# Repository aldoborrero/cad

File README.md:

# cad

My CAD projects in one repo, with the toolchain pinned so a checkout builds the same
parts on any machine.

Every part is **source, not a binary**: an OpenSCAD script, a FreeCAD Python model, or a
KiCad project. Parts diff and merge like code, the numbers behind them are readable, and
everything under `exports/` is rebuilt on demand rather than committed.

## What's here

**Three kernels, because none of them is good at everything.** A part lives with the tool
that suits it, and a part that wants two of them gets two:

| | Good at | Entry file |
|---|---|---|
| **OpenSCAD** | fast parametric iteration, mesh/CSG | `<project>/openscad/<project>.scad` |
| **FreeCAD** (Python) | OCCT **B-rep** — real fillets and chamfers, native STEP | `<project>/freecad/<project>.py` |
| **KiCad** | the electrical side; hands the board to the other two as STEP | `<project>/kicad/<project>.kicad_pro` |

**One reproducible shell.** `nix develop` gives you all three plus the OpenSCAD libraries
(BOSL2, Round-Anything), a linter, and the export tooling — no system installs, same
versions everywhere.

**One command for the boring parts.** `cad export`, `cad render`, `cad gui`, `cad new`
work the same whichever kernel a project uses.

**ECAD meets MCAD.** FreeCAD carries the [KiCadStepUp][ksu] workbench, wired to KiCad's
3D model library, so a board opens in FreeCAD with its components on it and mechanical
constraints can travel back to the board outline.

**Two MCP servers**, so an LLM can drive either kernel: `freecad-mcp` for FreeCAD, and
[Konnect][kon] for KiCad — 187 tools over KiCad 10's official IPC API, loaded on demand.
Both are on PATH in the devshell; register them with your MCP client. Don't run `konnect`
bare in a terminal — it reads a TTY as "install yourself into `~/.claude`".

[ksu]: https://github.com/easyw/kicadStepUpMod
[kon]: https://github.com/mixelpixx/Konnect

## Projects

| Project | Kernels | What it is |
|---|---|---|
| [**marble-run**](projects/marble-run/openscad/) | OpenSCAD (+ FreeCAD for one piece) | A 3D-printable **Hape Quadrilla**-compatible marble run: **34 parts** across blocks, rails, ramps, connectors, mechanisms, towers and catchers, all derived from one measured set of dimensions (`SIDE=44`, `HEIGHT=60`, Ø16 marble). Channel geometry is a faithful port of [`shuckc/quadri-plot`][qp]. Ships a `pybullet` bench that drops marbles through the mechanisms, and a checker that builds every part and asserts on its mesh. |
| [**iotorero-mount**](projects/iotorero-mount/) | OpenSCAD + FreeCAD | Outlet cradle for the round Athom / IoTorero IR remote (RF + IR, USB-C, ~20 g). It rests on the USB charger in a Schuko socket, with the puck hanging below and spare cable in a snap-in clip. Built **twice**, once per kernel, as a side-by-side mesh-vs-B-rep reference. |

[qp]: https://github.com/shuckc/quadri-plot

> The charger-brick dimensions in `iotorero-mount` (`BRICK_W` / `BRICK_H`) are
> placeholders — measure yours before printing.

## Getting started

```sh
direnv allow          # .envrc: `use flake` + `PATH_add bin`
# ...or, without direnv:
nix develop           # then run ./bin/cad
```

```sh
cad ls                            # what's in here
cad export marble-run             # STL + 3MF into projects/marble-run/openscad/exports/
cad render iotorero-mount/openscad side
cad gui marble-run
```

## The `cad` helper

An optional [KiCad Backplane package](docs/kicad-backplane.md) supplies a
headless IPC server: `nix run .#kicad-backplane -- api-server --help`.
It is built separately and does not replace KiCad on the devshell PATH.

| Command | Does |
|---|---|
| `cad ls` | list every project, as `project/tool` |
| `cad new openscad\|freecad\|kicad NAME` | scaffold from `templates/<tool>/` |
| `cad render NAME [VIEW]` | PNG preview → `exports/` (OpenSCAD and KiCad) |
| `cad export NAME` | OpenSCAD → STL + 3MF · FreeCAD → STEP + STL · KiCad → STEP |
| `cad step NAME` | OpenSCAD → STEP via FreeCAD (best-effort) |
| `cad gui NAME` | open in OpenSCAD / FreeCAD / KiCad |

`NAME` is a path under `projects/` with the tool part optional: `marble-run`,
`marble-run/ramps/accelerator`, `iotorero-mount/openscad`. A bare name resolves by itself
when only one kernel has the part, and asks you to say which when both do.

`VIEW` is a camera for OpenSCAD (`iso|fit|top|front|side`) and a side of the board for
KiCad (`iso|top|bottom|front|back|left|right`).

## Layout

```
projects/<project>/{openscad,freecad,kicad}/    the parts; exports/ is generated
templates/{openscad,freecad,kicad}/             what `cad new` copies
lib/openscad/                                   shared helpers: `use <common.scad>`
bin/cad                                         the helper
nix/                                            devshell, packages, checks
```

A tool directory holds only that kernel's source. A project with tooling of its own keeps
it one level up, beside them — `marble-run` has `sim/` and `tools/` (Python that drives
OpenSCAD) plus a `bin/` and an `.envrc`, so `cd projects/marble-run` and `play` or `check`
are on PATH.

Project-first on purpose: a part that exists in two kernels is *one* directory with both
inside, not the same name in two corners of the repo.

Source of truth is the `.scad` / `.py` / the KiCad project files. Everything under
`exports/` is generated and git-ignored — don't commit it.

## Licensing

The parts in `projects/` are mine. Everything the devshell pulls in is somebody else's
and keeps its own licence — this repo packages it, it does not relicense it.

The table below is **generated from the flake**, so it cannot drift from what is actually
installed: `nix run .#update-licenses` regenerates it, and `nix flake check` fails both
when it is stale and when an input has been added that `nix/lib/default.nix` does not
classify. Copyleft licences are bolded, since those are the ones worth noticing.

<!-- BEGIN LICENCES -->
<!-- Generated by `nix run .#update-licenses`. Do not edit by hand. -->

### On PATH in the devshell

| | Licence | What it is |
|---|---|---|
| [ShellCheck](https://hackage.haskell.org/package/ShellCheck) 0.11.0 | **GPL-3.0-only** | Shell script analysis tool |
| [freecad](https://www.freecad.org) 1.1.1 | LGPL-2.0-or-later | General purpose Open Source 3D CAD/MCAD/CAx/CAE/PLM modeler, with the MCP and Gridfinity workbenches and this repo's preferences |
| [freecad-mcp](https://github.com/neka-nat/freecad-mcp) 0.1.21 | MIT | MCP server for FreeCAD: drives a running FreeCAD over XML-RPC |
| [freerouting](https://www.freerouting.org) 2.2.4 | **GPL-3.0-only** | Advanced PCB auto-router |
| [kicad](https://www.kicad.org/) 10.0.4 | **GPL-3.0-or-later** | Open Source Electronics Design Automation suite |
| [konnect](https://github.com/mixelpixx/Konnect) 0.11.0 | **AGPL-3.0-only** | MCP server for KiCad 10: drives a running KiCad over its IPC API |
| [openscad-lsp](https://github.com/Leathong/openscad-LSP) 2.0.2 | Apache-2.0 | LSP (Language Server Protocol) server for OpenSCAD |
| [openscad-unstable](https://openscad.org/) 2021.01-unstable-2026-07-20 | **GPL-3.0** | 3D parametric model compiler (unstable) |
| [orca-slicer](https://github.com/OrcaSlicer/OrcaSlicer) 2.4.2 | **AGPL-3.0-only** | G-code generator for 3D printers (Bambu, Prusa, Voron, VzBot, RatRig, Creality, etc.) |
| [python3](https://www.python.org) | Python-2.0 | High-level dynamically-typed programming language |
| [sca2d](https://gitlab.com/bath_open_instrumentation_group/sca2d) 0.2.2 | **GPL-3.0-only** | Experimental static code analyser for OpenSCAD |
| [xvfb-run](https://github.com/archlinux/svntogit-packages) 1+g87f6705 | **GPL-2.0-only** | Convenience script to run a virtualized X-Server |

### Optional packages (not on the devshell PATH)

| | Licence | What it is |
|---|---|---|
| [kicad-backplane](https://github.com/i2cjak/Backplane_KiCad) 10.0.6-backplane-1c193606edde | **GPL-3.0-or-later** | KiCad 10.0.6 with Backplane headless PCB and schematic IPC backports |

### Vendored as source (FreeCAD addons, OpenSCAD libraries)

| | Licence | What it is |
|---|---|---|
| [bosl2](https://github.com/BelfrySCAD/BOSL2) | BSD-2-Clause | OpenSCAD library: rounded solids, attachments, threads, gears |
| [curves](https://github.com/tomate44/CurvesWB) | LGPL-2.0 | FreeCAD workbench: NURBS curve and surface tools |
| [gridfinity](https://github.com/Stu142/FreeCAD-Gridfinity-Workbench) | LGPL-2.0 | FreeCAD workbench: Gridfinity storage bins |
| [kicad-stepup](https://github.com/easyw/kicadStepUpMod) | **AGPL-3.0** | FreeCAD workbench: bidirectional KiCad <-> FreeCAD (ECAD/MCAD) |
| [round-anything](https://github.com/Irev-Dev/Round-Anything) | MIT | OpenSCAD library: 2D/3D rounding (polyRound) |
<!-- END LICENCES -->

Two worth knowing about. **Konnect is AGPL-3.0** — free for individuals and open source,
commercial licences sold separately — so it is the one to check before using it at work.
And **KiCadStepUp declares AGPLv3 in its `package.xml` but ships no `LICENSE` file**, so
the full text is not in the tree.

This repo itself carries no `LICENSE`, which under copyright law means all rights
reserved. That is the default, not a decision; add one if you ever publish it.

## Notes to self

[`CLAUDE.md`](CLAUDE.md) is the long-form version of all of the above: the conventions,
and a **Gotchas** section recording the traps that cost real time here (OpenSCAD's
Manifold backend, BOSL2's globals shadowing, FreeCAD's addon and preference mechanics,
KiCad's compressed 3D models). [`CHANGELOG.md`](CHANGELOG.md) has what changed and why.

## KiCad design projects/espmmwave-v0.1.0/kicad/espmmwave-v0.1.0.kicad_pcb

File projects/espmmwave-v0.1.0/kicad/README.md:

# espmmwave-v0.1.0 (KiCad)

The board and schematic for the ESPHome LD2450 presence sensor. **The project manual —
bill of materials, datasheets, differences from the original and credits — is one level up
in [`../README.md`](../README.md).** This file covers only what is specific to the KiCad
half.

The usual trio, all sharing the project's name: `espmmwave-v0.1.0.kicad_pro`,
`.kicad_sch` and `.kicad_pcb`, plus this project's own libraries — `espmmwave.kicad_sym`
and `espmmwave.pretty/` — which hold the XIAO ESP32S3 symbol and footprint that KiCad does
not ship.

## Both files are source; the geometry can still be rebuilt

**`.kicad_pcb` is edited.** It can be *rebuilt* from the measured geometry in
`../tools/board.py`, which parses it out of the original's gerbers — something KiCad has no
way to do — but that is a bootstrap, not the daily path.

```sh
board --regenerate   # -> .kicad_pcb, from the measured geometry and the schematic's netlist
```

**Both files are edited and kept**, in eeschema and pcbnew or through the Konnect MCP
server. They began life generated, which is why they agree, but that is now a property to be
*checked* rather than one the tooling can guarantee:

```sh
check        # the everyday command: do the board and the sheet still agree?
```

`board` refuses to write without `--regenerate`: it rebuilds the whole file and every run
mints fresh UUIDs, so there is nothing to merge — what it writes replaces everything. There
is no schematic generator any more; eeschema and Konnect both write schematics perfectly
well, and one description of the circuit is enough.

## Checking it

`check` runs three checks, and they fail for different reasons:

| Check | Catches |
|---|---|
| connectivity | the board's pad-to-net assignment, against the netlist KiCad exports from the sheet |
| annotation | every symbol's instance reference and root-sheet path |
| ERC | KiCad's own electrical rules |

The middle one is not redundant. **`kicad-cli sch erc` resolves a symbol's reference from its
`Reference` property, while eeschema resolves it from the `instances` block** — so a file can
report 0 violations and still open full of duplicate, unannotated `#PWR?` symbols. That is a
defect this project actually shipped; the repo's `CLAUDE.md` records the trap. Run ERC in the
GUI too.

The board keeps its own:

```sh
kicad-cli pcb drc --severity-all -o /tmp/drc.rpt espmmwave-v0.1.0.kicad_pcb
```

## Handoff to the mechanical side

```sh
cad export espmmwave-v0.1.0     # -> exports/espmmwave-v0.1.0.step
cad render espmmwave-v0.1.0 iso # -> exports/espmmwave-v0.1.0-iso.png
```

The STEP is what FreeCAD opens to check the board against the Hammond 1551V3GY case and the
LD2450 bracket. Importing the `.kicad_pcb` directly with the **KiCadStepUp** workbench works
too, and resolves each footprint's 3D model against the library the devshell's `kicad`
ships.

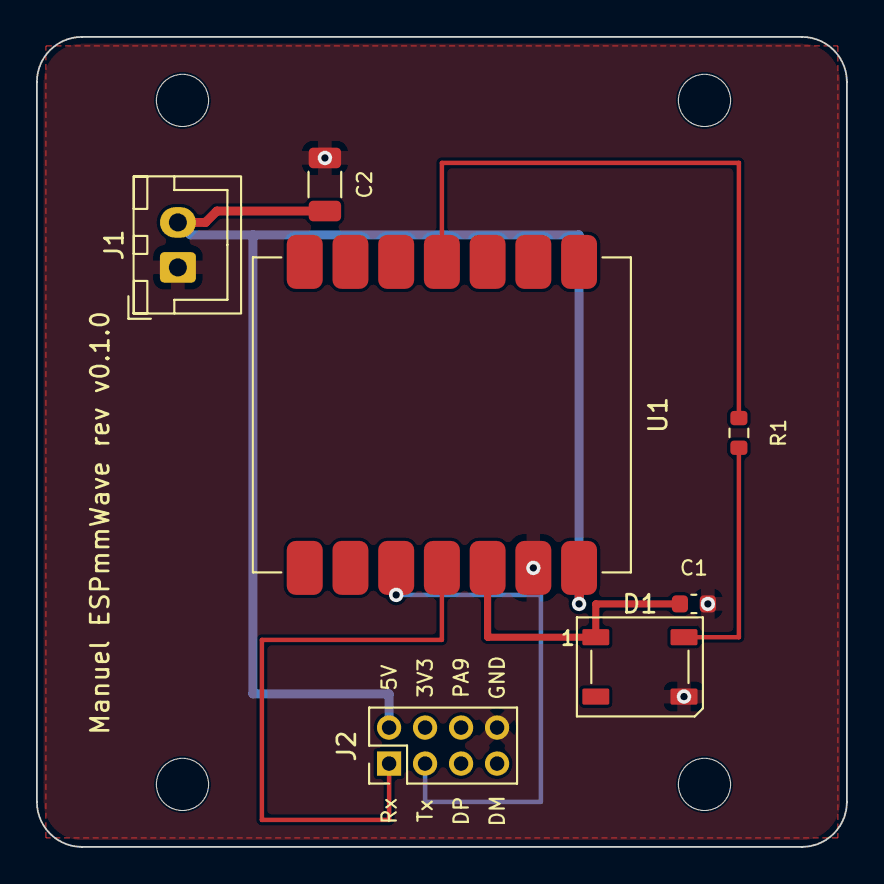
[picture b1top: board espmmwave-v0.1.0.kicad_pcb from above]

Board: 2 copper layers, 45.0 x 45.0 mm, 7 parts (0 on the bottom side), 7 nets.

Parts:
C1: C_0603_1608Metric
C2: C_1206_3216Metric
D1: LED_WS2812B_PLCC4_5.0x5.0mm_P3.2mm
J1: JST_XH_B2B-XH-A_1x02_P2.50mm_Vertical
J2: PinHeader_2x04_P2.00mm_Vertical
R1: R_0603_1608Metric
U1: XIAO_ESP32S3

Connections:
+3V3: C1.1, D1.1, U1.3V3
+5V: C2.1, J1.2, J2.2, U1.5V
GND: C1.2, C2.2, D1.3, J1.1, J2.8, U1.GND
LED_DATA: R1.2, U1.D3
LED_DIN: D1.4, R1.1
RADAR_RX: J2.1, U1.D10
RADAR_TX: J2.3, U1.D9

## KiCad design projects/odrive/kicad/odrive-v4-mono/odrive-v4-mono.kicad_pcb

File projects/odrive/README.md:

# odrive (KiCad)

ODrive brushless motor controller: a faithful KiCad 10 recreation of the v3.5
schematic, and a v4 redesign derived from it.

Upstream: [madcowswe/ODriveHardware](https://github.com/madcowswe/ODriveHardware)
(Altium sources; we work from a local fork clone). Firmware is open source (MIT) at
odriverobotics/ODrive up to v0.5.6, which supports every v3.x board.

## Layout

```
docs/
  v3.5-weaknesses.md    # audited weak points of the v3.5 design (workflow phase: Audit)
  v4-design.md          # v4 design decisions with rationale (workflow phase: Design)
kicad/
  odrive-v3.5/          # faithful v3.5 schematic (no PCB) — the audited baseline
  odrive-v4/            # the v4: schematic + 4-layer board
workflow/
  e2e.js                # oracle-gated end-to-end Workflow script (see below)
```

Reference material lives in `.scratch/odrive/` at the repo root (gitignored, per repo
convention): `schematic_v3.5.pdf` (the 24V variant), `CHANGELOG.md`, board photos, and
`netlist-ref/` (netlist ground truth extracted from the PDF by the workflow). Refresh
from `/mnt/c/Users/aldob/dev/ODriveHardware/v3/` if missing.

## Scope decisions (2026-09-03)

- **Architecture: modernized.** Keep STM32F405RGT6 (firmware nearly intact); replace
  the NRND DRV8301 with DRV8353RS (100 V, SPI, integrated buck + 3 CSAs); modern FETs;
  USB-C; better CAN; add the protections v3.5 lacks.
- **Bus voltage: both variants.** One design, two BOMs — 24 V and 56 V.
- **v3.5 conversion: faithful schematic only.** Clean ERC, netlist checked against the
  PDF (which embeds the Altium netlist as text). No v3 PCB recreation.
- **Form factor: free.** Connectors and dimensions optimized, not v3.5-compatible.

## The end-to-end workflow

`workflow/e2e.js` drives the whole flow with oracle gates: every phase's output is
verified by adversarial/judge agents before the next phase consumes it. Phases:

| Phase | Needs | Output |
|-------|-------|--------|
| Gate | — | Konnect MCP + KiCad IPC availability |
| Audit | PDF only | `docs/v3.5-weaknesses.md` (findings, adversarially verified) |
| Design | Audit | `docs/v4-design.md` (judge panel: electrical / firmware / manufacturability) |
| Extract | PDF only | `.scratch/odrive/netlist-ref/*.json` (ground truth per sheet) |
| Rebuild | Konnect | v3.5 schematic in KiCad; oracle diffs exported netlist vs ground truth |
| V4Schematic | Konnect | v4 schematic; ERC + design-review oracle loop |
| Layout | Konnect + KiCad IPC | v4 4-layer board; DRC oracle loop |
| Fab | Layout done | gerbers, 24V/56V BOMs, pick-and-place in `kicad/odrive-v4/exports/` |

Phases that need tools this session lacks are skipped with a `blocked` status and
instructions; re-running the workflow resumes where it left off (completed outputs are
detected on disk).

**Konnect requirement:** the Konnect MCP server is registered in this repo's
`.mcp.json`, so the Claude session must be started *inside this worktree* (direnv puts
`konnect` on PATH). For the Layout phase, KiCad's IPC API must be live: start KiCad
(GUI, or `xvfb-run kicad` headless) with the API server enabled
(socket `ipc:///tmp/kicad/api.sock`).

## Build

```sh
cad render odrive/kicad/odrive-v4 [iso|top|bottom|...]   # raytraced PNG -> exports/
cad export odrive/kicad/odrive-v4                        # STEP -> exports/
cad gui    odrive/kicad/odrive-v4                        # open in KiCad
```

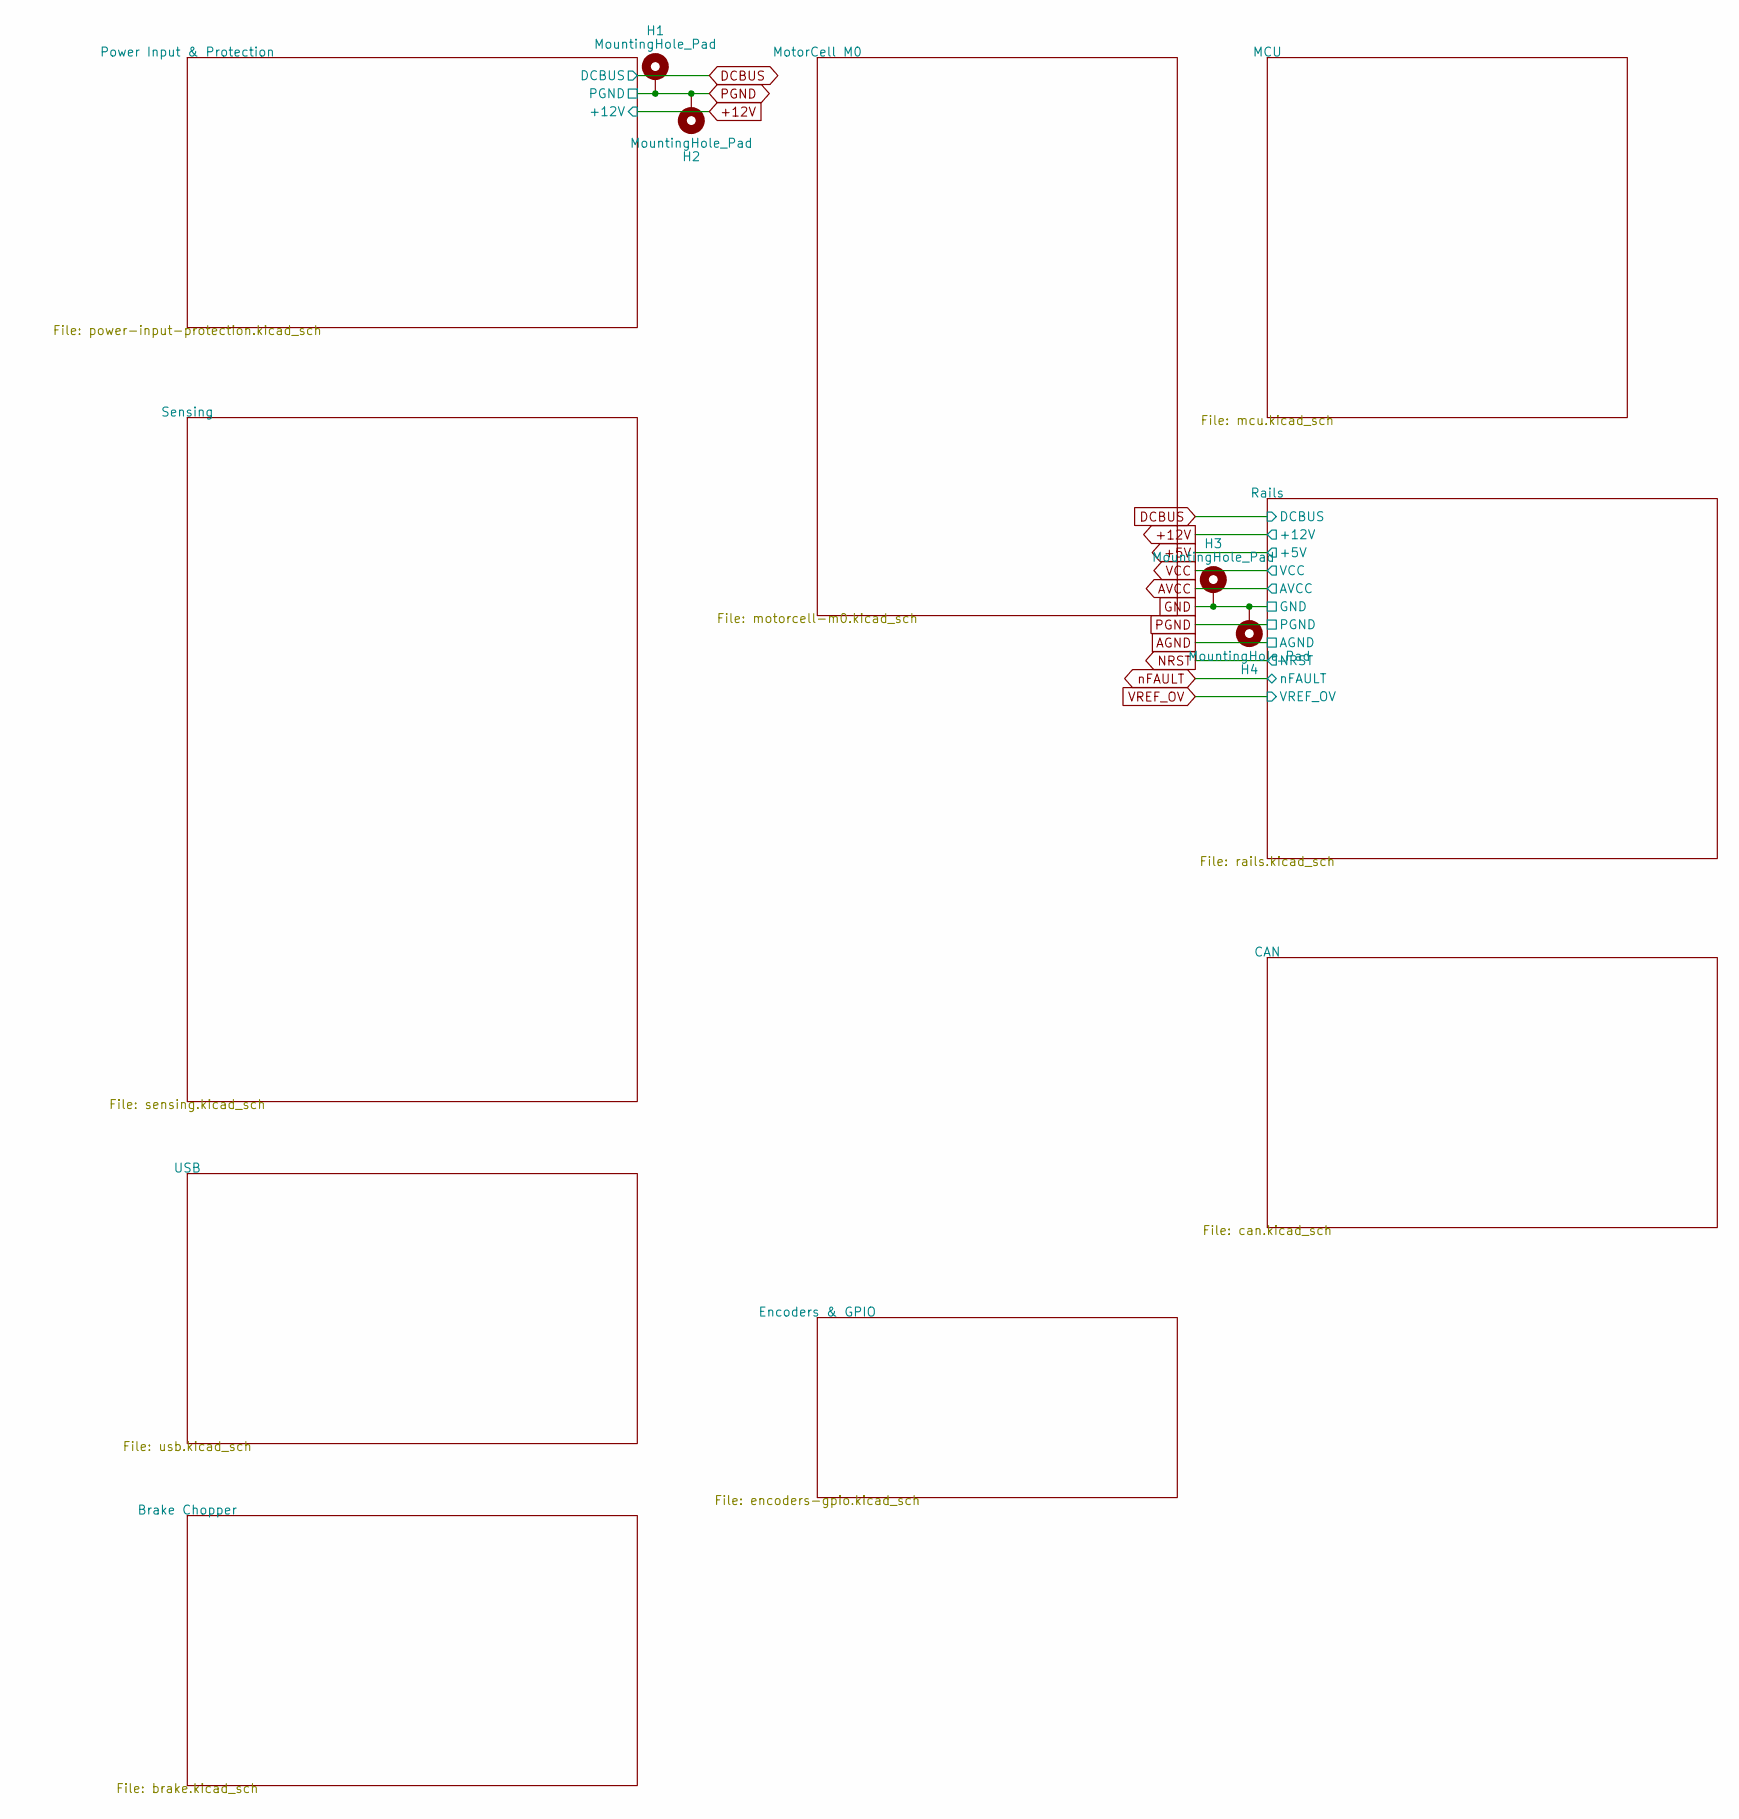
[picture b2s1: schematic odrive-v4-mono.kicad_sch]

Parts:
H1, H2, H3, H4: MountingHole_Pad; MountingHole_3.2mm_M3_Pad

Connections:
GND: H3.1, H4.1; also elsewhere on the board
PGND: H1.1, H2.1; also elsewhere on the board

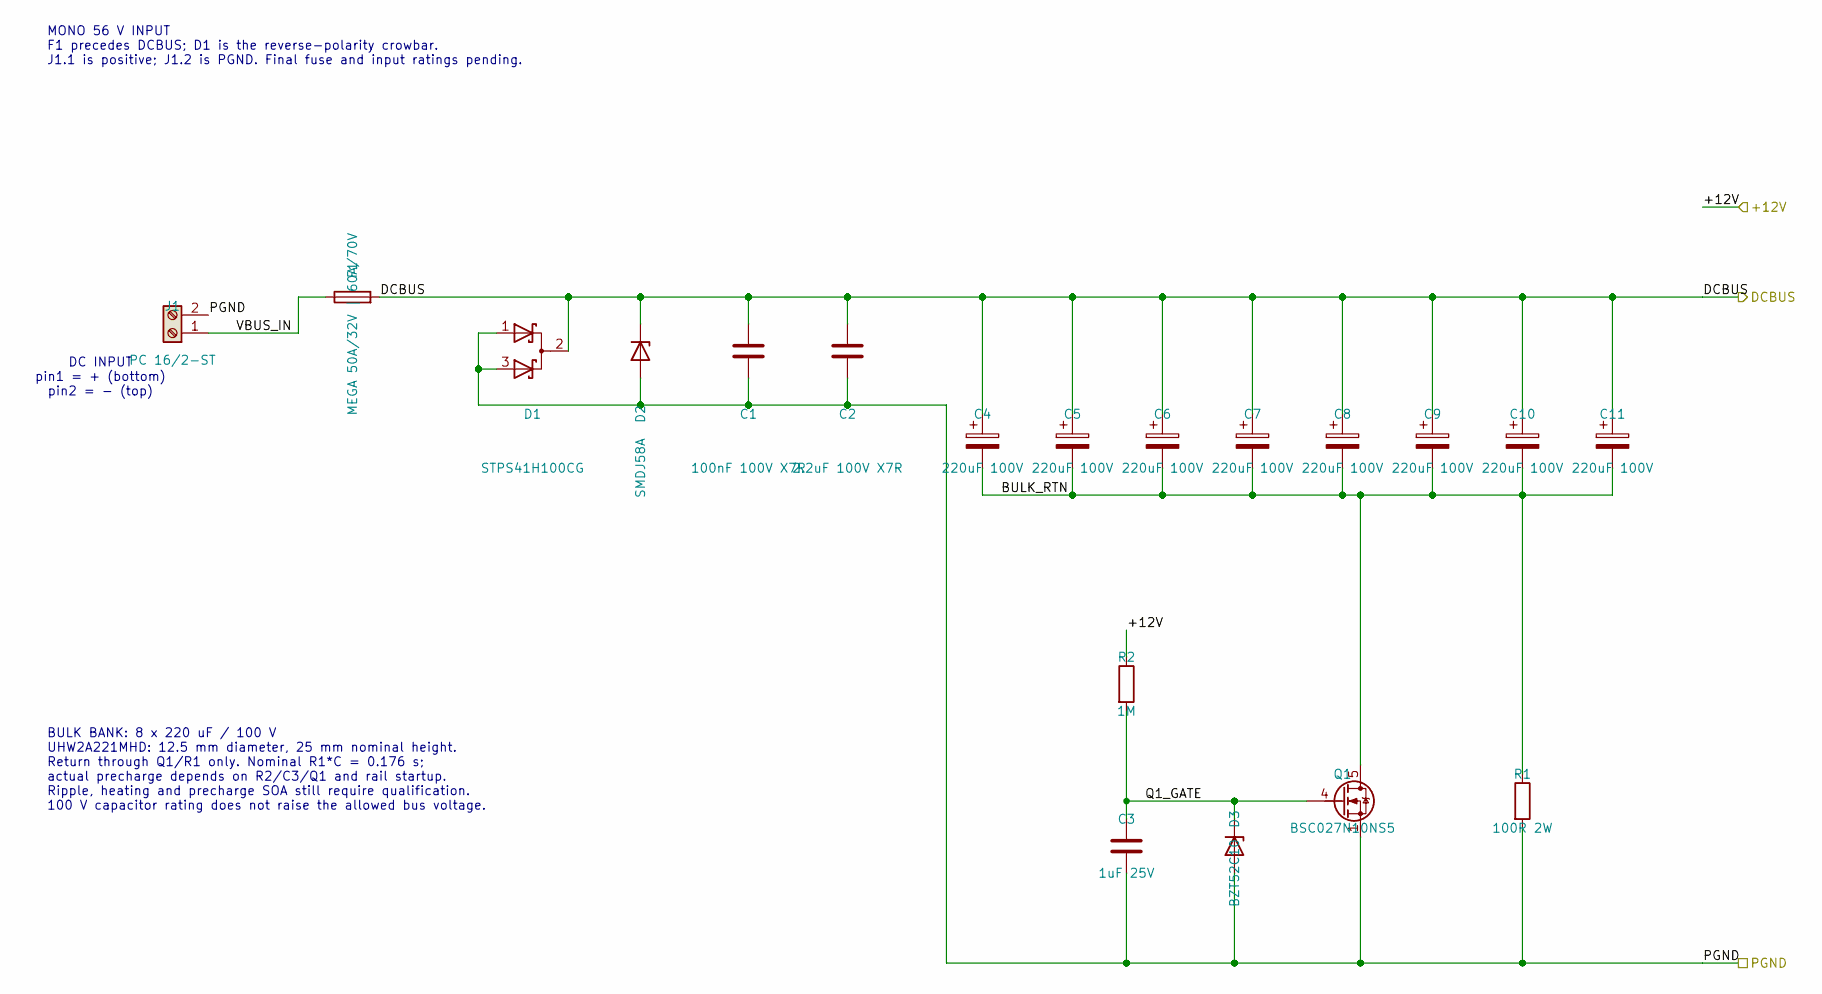
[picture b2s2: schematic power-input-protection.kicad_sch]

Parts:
C1: 100nF 100V X7R; C_0603_1608Metric
C2: 2.2uF 100V X7R; C_1210_3225Metric
C3: 1uF 25V; C_0603_1608Metric
C4, C5, C6, C7, C8, C9, C10, C11: 220uF 100V; CP_Radial_D12.5mm_P5.00mm; Tolerance 20%; Voltage 100 V; MPN_56V UHW2A221MHD
D1: STPS41H100CG; TO-263-3_TabPin2; MPN STPS41H100CG-TR
D2: SMDJ58A; D_SMC; MPN_24V SMDJ28A
D3: BZT52C10; D_SOD-123; MPN BZT52C10
F1: MEGA 50A/32V | 60A/70V; Fuse_Littelfuse_MEGA_BoltDown; MPN_24V Littelfuse 0298050.ZXEH (50A/32V)
J1: PC 16/2-ST; TerminalBlock_Phoenix_PC-16-2-ST-10.16mm; MPN Phoenix PC 16/2-ST-10,16
Q1: BSC027N10NS5; Infineon_PG-TSON-8-3; MPN_56V BSC027N10NS5ATMA1
R1: 100R 2W; R_2512_6332Metric
R2: 1M; R_0603_1608Metric

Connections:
+12V: R2.1; also elsewhere on the board
/Power Input & Protection/BULK_RTN: C4.2, C5.2, C6.2, C7.2, C8.2, C9.2, C10.2, C11.2, Q1.5 (D), R1.1
/Power Input & Protection/Q1_GATE: C3.1, D3.1 (K), Q1.4 (G), R2.2
/Power Input & Protection/VBUS_IN: F1.1, J1.1
DCBUS: C1.1, C2.1, C4.1, C5.1, C6.1, C7.1, C8.1, C9.1, C10.1, C11.1, D1.2 (K), D2.1 (K), F1.2; also elsewhere on the board
PGND: C1.2, C2.2, C3.2, D1.1 (A), D1.3 (A), D2.2 (A), D3.2 (A), J1.2, Q1.1 (S), Q1.2 (S), Q1.3 (S), R1.2; also elsewhere on the board

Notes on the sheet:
DC INPUT pin1 = + (bottom) pin2 = - (top)
MONO 56 V INPUT F1 precedes DCBUS; D1 is the reverse-polarity crowbar. J1.1 is positive; J1.2 is PGND. Final fuse and input ratings pending.
BULK BANK: 8 x 220 uF / 100 V UHW2A221MHD: 12.5 mm diameter, 25 mm nominal height. Return through Q1/R1 only. Nominal R1*C = 0.176 s; actual precharge depends on R2/C3/Q1 and rail startup. Ripple, heating and precharge SOA still require qualification. 100 V capacitor rating does not raise the allow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

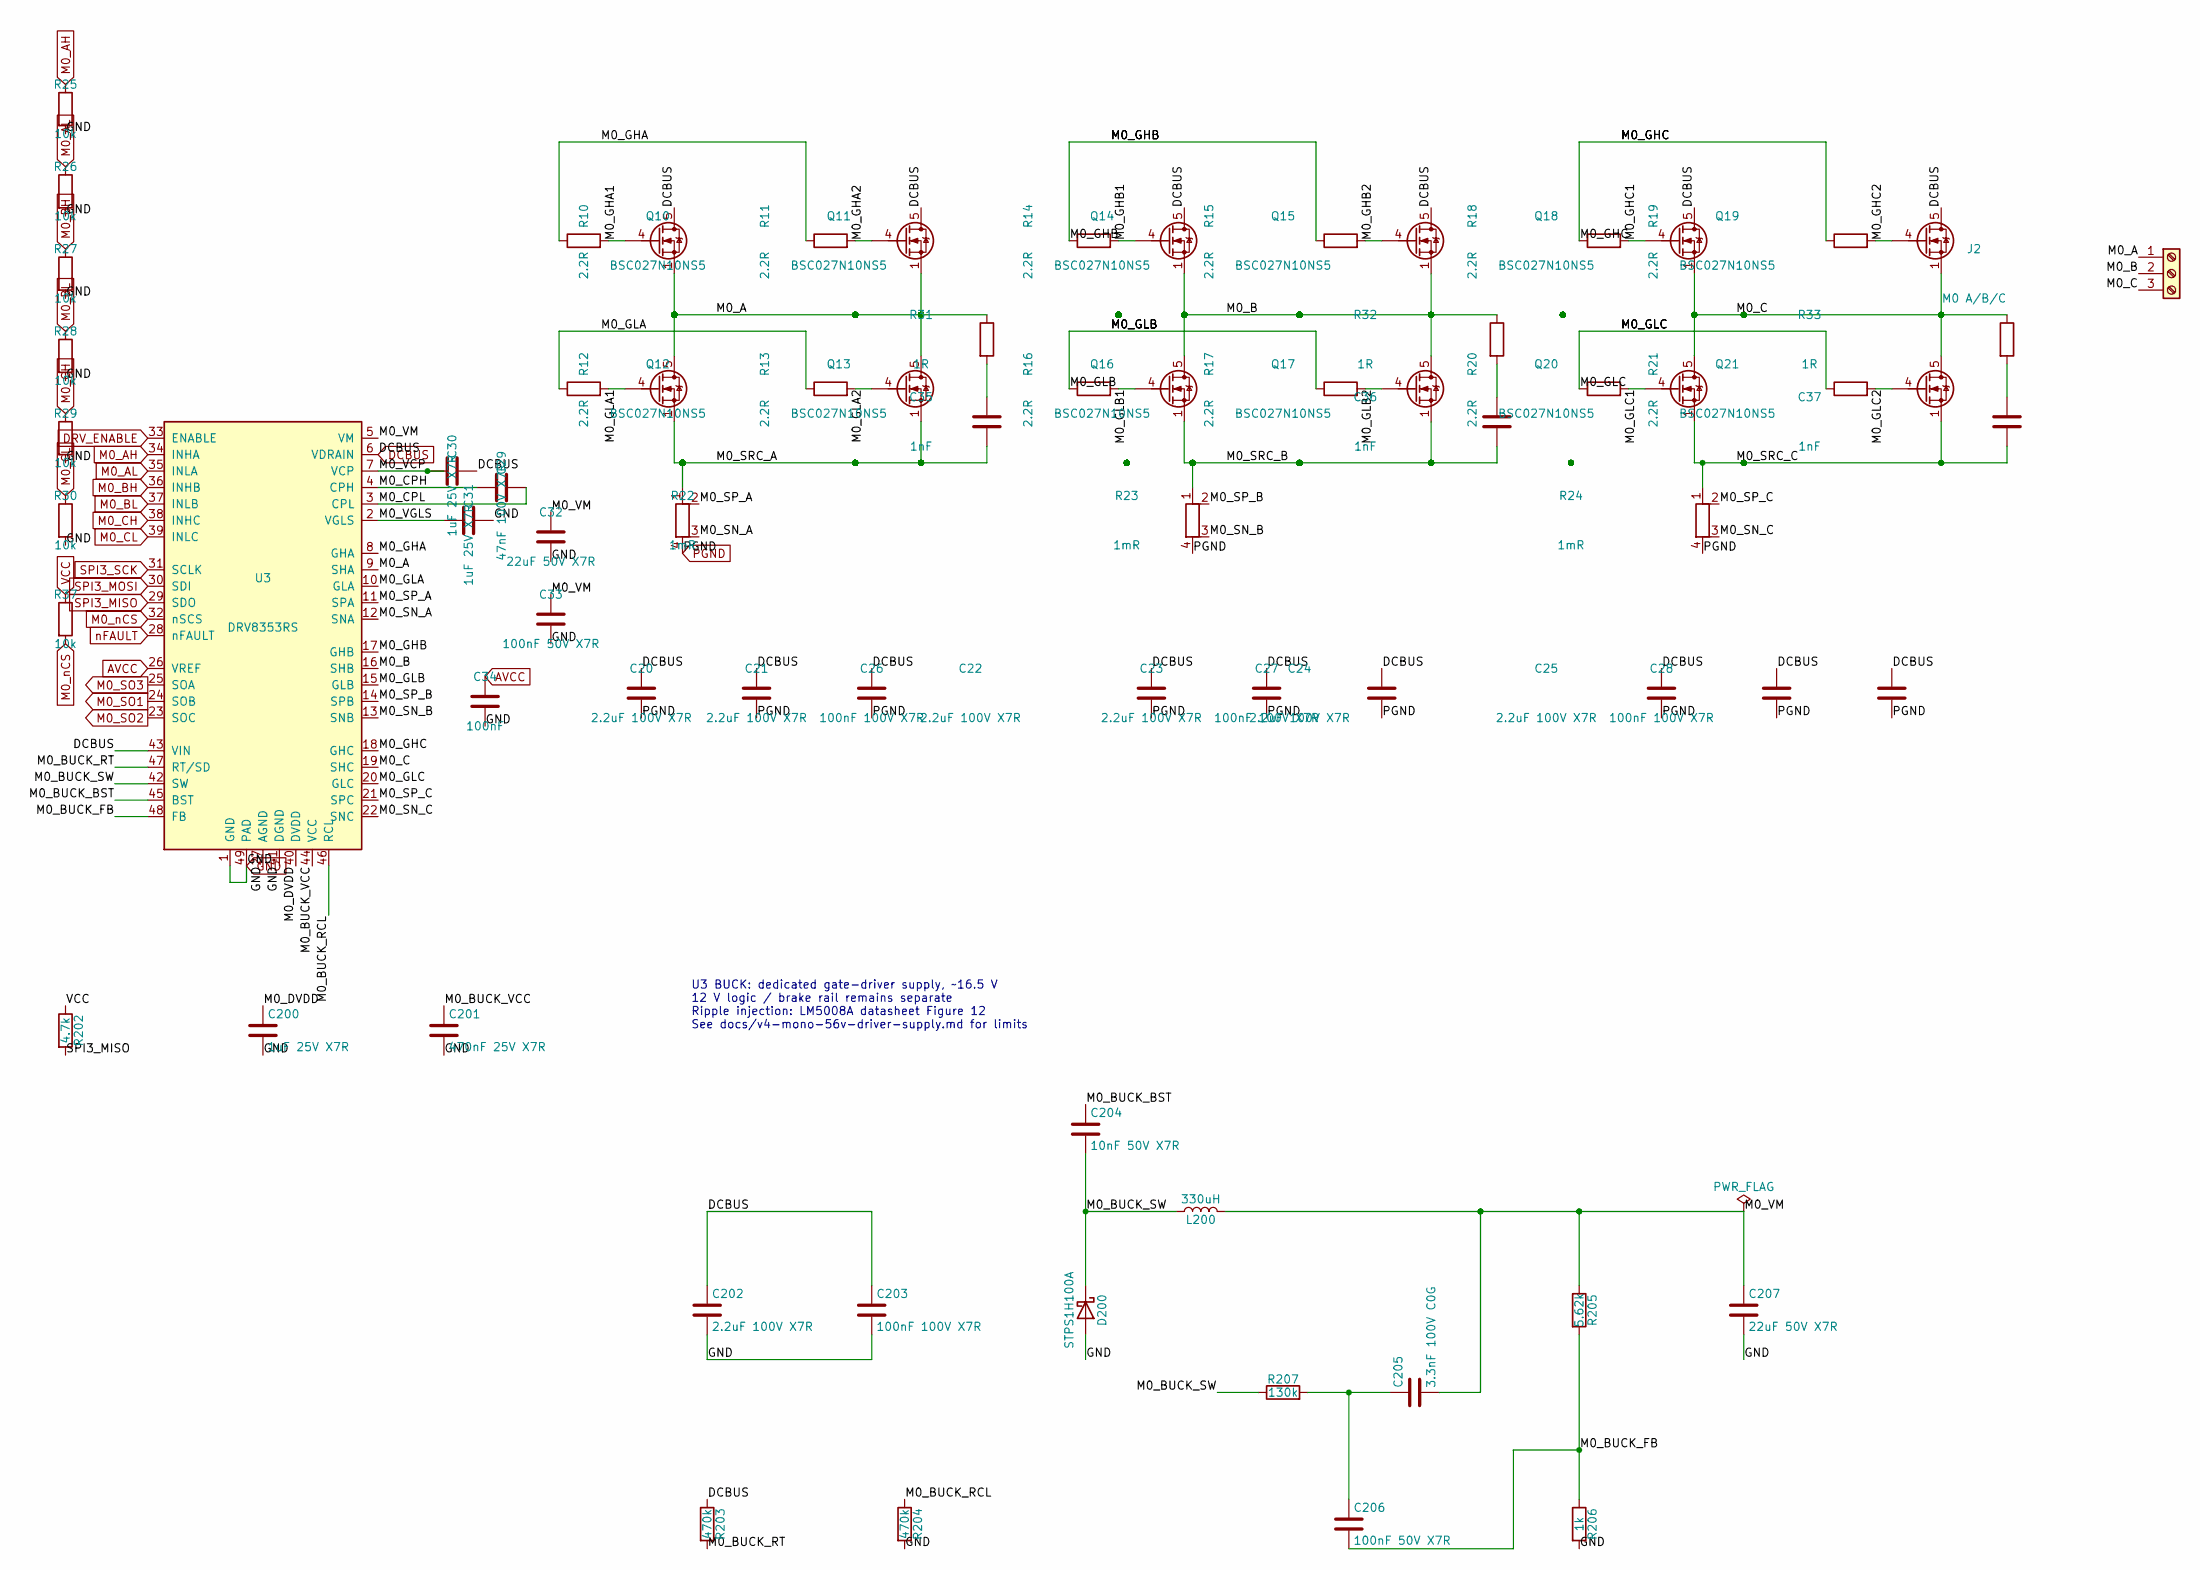
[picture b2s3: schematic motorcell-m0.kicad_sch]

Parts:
C20, C21, C22, C23, C24, C25: 2.2uF 100V X7R; C_1210_3225Metric
C26, C27, C28: 100nF 100V X7R; C_0603_1608Metric
C29: 47nF 100V X7R; C_0805_2012Metric
C30, C31, C200: 1uF 25V X7R; C_0603_1608Metric
C32: 22uF 50V X7R; C_1210_3225Metric
C33: 100nF 50V X7R; C_0603_1608Metric
C34: 100nF; C_0603_1608Metric
C35, C36, C37: 1nF; C_0603_1608Metric
C201: 470nF 25V X7R; C_0603_1608Metric
C202: 2.2uF 100V X7R; C_1210_3225Metric; Tolerance 20%
C203: 100nF 100V X7R; C_0603_1608Metric; Tolerance 20%
C204: 10nF 50V X7R; C_0603_1608Metric; Tolerance 5%
C205: 3.3nF 100V C0G; C_0603_1608Metric; Tolerance 5%
C206: 100nF 50V X7R; C_0603_1608Metric; Tolerance 20%
C207: 22uF 50V X7R; C_1210_3225Metric; Tolerance 20%
D200: STPS1H100A; D_SMA; Tolerance 20%; MPN STPS1H100A
J2: M0 A/B/C; TerminalBlock_Phoenix_PC-16-3-ST-10.16mm
L200: 330uH; L_Bourns_SRR1260; Tolerance 10%; MPN SRR1260-331K
Q10, Q11, Q12, Q13, Q14, Q15, Q16, Q17, Q18, Q19, Q20, Q21: BSC027N10NS5; Infineon_PG-TSON-8-3; MPN BSC027N10NS5ATMA1
R10, R11, R12, R13, R14, R15, R16, R17, R18, R19, R20, R21: 2.2R; R_0603_1608Metric
R22, R23, R24: 1mR; R_Shunt_Vishay_WSK2512_6332Metric_T2.66mm
R25, R26, R27, R28, R29, R30, R37: 10k; R_0603_1608Metric
R31, R32, R33: 1R; R_0603_1608Metric
R202: 4.7k; R_0603_1608Metric
R203: 470k; R_0805_2012Metric; Tolerance 1%
R204: 470k; R_0603_1608Metric; Tolerance 1%
R205: 5.62k; R_0603_1608Metric; Tolerance 1%
R206: 1k; R_0603_1608Metric; Tolerance 1%
R207: 130k; R_0805_2012Metric; Tolerance 1%
U3: DRV8353RS; QFN-48-1EP_7x7mm_P0.5mm_EP5.15x5.15mm_ThermalVias; MPN DRV8353RSRGZR

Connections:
/MotorCell M0/M0_A: J2.1, Q10.1 (S), Q10.2 (S), Q10.3 (S), Q11.1 (S), Q11.2 (S), Q11.3 (S), Q12.5 (D), Q13.5 (D), R31.1, U3.9 (SHA)
/MotorCell M0/M0_B: J2.2, Q14.1 (S), Q14.2 (S), Q14.3 (S), Q15.1 (S), Q15.2 (S), Q15.3 (S), Q16.5 (D), Q17.5 (D), R32.1, U3.16 (SHB)
/MotorCell M0/M0_BUCK_BST: C204.1, U3.45 (BST)
/MotorCell M0/M0_BUCK_FB: C206.2, R205.2, R206.1, U3.48 (FB)
/MotorCell M0/M0_BUCK_RCL: R204.1, U3.46 (RCL)
/MotorCell M0/M0_BUCK_RT: R203.2, U3.47 (RT/SD)
/MotorCell M0/M0_BUCK_SW: C204.2, D200.1 (K), L200.1, R207.1, U3.42 (SW)
/MotorCell M0/M0_BUCK_VCC: C201.1, U3.44 (VCC)
/MotorCell M0/M0_C: J2.3, Q18.1 (S), Q18.2 (S), Q18.3 (S), Q19.1 (S), Q19.2 (S), Q19.3 (S), Q20.5 (D), Q21.5 (D), R33.1, U3.19 (SHC)
/MotorCell M0/M0_CPH: C29.1, U3.4 (CPH)
/MotorCell M0/M0_CPL: C29.2, U3.3 (CPL)
/MotorCell M0/M0_DVDD: C200.1, U3.40 (DVDD)
/MotorCell M0/M0_GHA: R10.1, R11.1, U3.8 (GHA)
/MotorCell M0/M0_GHA1: Q10.4 (G), R10.2
/MotorCell M0/M0_GHA2: Q11.4 (G), R11.2
/MotorCell M0/M0_GHB: R14.1, R15.1, U3.17 (GHB)
/MotorCell M0/M0_GHB1: Q14.4 (G), R14.2
/MotorCell M0/M0_GHB2: Q15.4 (G), R15.2
/MotorCell M0/M0_GHC: R18.1, R19.1, U3.18 (GHC)
/MotorCell M0/M0_GHC1: Q18.4 (G), R18.2
/MotorCell M0/M0_GHC2: Q19.4 (G), R19.2
/MotorCell M0/M0_GLA: R12.1, R13.1, U3.10 (GLA)
/MotorCell M0/M0_GLA1: Q12.4 (G), R12.2
/MotorCell M0/M0_GLA2: Q13.4 (G), R13.2
/MotorCell M0/M0_GLB: R16.1, R17.1, U3.15 (GLB)
/MotorCell M0/M0_GLB1: Q16.4 (G), R16.2
/MotorCell M0/M0_GLB2: Q17.4 (G), R17.2
/MotorCell M0/M0_GLC: R20.1, R21.1, U3.20 (GLC)
/MotorCell M0/M0_GLC1: Q20.4 (G), R20.2
/MotorCell M0/M0_GLC2: Q21.4 (G), R21.2
/MotorCell M0/M0_SN_A: R22.3, U3.12 (SNA)
/MotorCell M0/M0_SN_B: R23.3, U3.13 (SNB)
/MotorCell M0/M0_SN_C: R24.3, U3.22 (SNC)
/MotorCell M0/M0_SP_A: R22.2, U3.11 (SPA)
/MotorCell M0/M0_SP_B: R23.2, U3.14 (SPB)
/MotorCell M0/M0_SP_C: R24.2, U3.21 (SPC)
/MotorCell M0/M0_SRC_A: C35.2, Q12.1 (S), Q12.2 (S), Q12.3 (S), Q13.1 (S), Q13.2 (S), Q13.3 (S), R22.1
/MotorCell M0/M0_SRC_B: C36.2, Q16.1 (S), Q16.2 (S), Q16.3 (S), Q17.1 (S), Q17.2 (S), Q17.3 (S), R23.1
/MotorCell M0/M0_SRC_C: C37.2, Q20.1 (S), Q20.2 (S), Q20.3 (S), Q21.1 (S), Q21.2 (S), Q21.3 (S), R24.1
/MotorCell M0/M0_VCP: C30.1, U3.7 (VCP)
/MotorCell M0/M0_VGLS: C31.1, U3.2 (VGLS)
/MotorCell M0/M0_VM: C32.1, C33.1, C205.2, C207.1, L200.2, R205.1, U3.5 (VM)
AVCC: C34.1, U3.26 (VREF); also elsewhere on the board
DCBUS: C20.1, C21.1, C22.1, C23.1, C24.1, C25.1, C26.1, C27.1, C28.1, C30.2, C202.1, C203.1, Q10.5 (D), Q11.5 (D), Q14.5 (D), Q15.5 (D), Q18.5 (D), Q19.5 (D), R203.1, U3.6 (VDRAIN), U3.43 (VIN); also elsewhere on the board
DRV_ENABLE: U3.33 (ENABLE); also elsewhere on the board
GND: C31.2, C32.2, C33.2, C34.2, C200.2, C201.2, C202.2, C203.2, C207.2, D200.2 (A), R25.2, R26.2, R27.2, R28.2, R29.2, R30.2, R204.2, R206.2, U3.1 (GND), U3.27 (AGND), U3.41 (DGND), U3.49 (PAD); also elsewhere on the board
M0_AH: R25.1, U3.34 (INHA); also elsewhere on the board
M0_AL: R26.1, U3.35 (INLA); also elsewhere on the board
M0_BH: R27.1, U3.36 (INHB); also elsewhere on the board
M0_BL: R28.1, U3.37 (INLB); also elsewhere on the board
M0_CH: R29.1, U3.38 (INHC); also elsewhere on the board
M0_CL: R30.1, U3.39 (INLC); also elsewhere on the board
M0_SO1: U3.24 (SOB); also elsewhere on the board
M0_SO2: U3.23 (SOC); also elsewhere on the board
M0_SO3: U3.25 (SOA); also elsewhere on the board
M0_nCS: R37.2, U3.32 (nSCS); also elsewhere on the board
unnamed: C35.1, R31.2
unnamed: C36.1, R32.2
unnamed: C37.1, R33.2
unnamed: C205.1, C206.1, R207.2
PGND: C20.2, C21.2, C22.2, C23.2, C24.2, C25.2, C26.2, C27.2, C28.2, R22.4, R23.4, R24.4; also elsewhere on the board
SPI3_MISO: R202.2, U3.29 (SDO); also elsewhere on the board
SPI3_MOSI: U3.30 (SDI); also elsewhere on the board
SPI3_SCK: U3.31 (SCLK); also elsewhere on the board
VCC: R37.1, R202.1; also elsewhere on the board
nFAULT: U3.28 (nFAULT); also elsewhere on the board

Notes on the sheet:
U3 BUCK: dedicated gate-driver supply, ~16.5 V 12 V logic / brake rail remains separate Ripple injection: LM5008A datasheet Figure 12 See docs/v4-mono-56v-driver-supply.md for limits
